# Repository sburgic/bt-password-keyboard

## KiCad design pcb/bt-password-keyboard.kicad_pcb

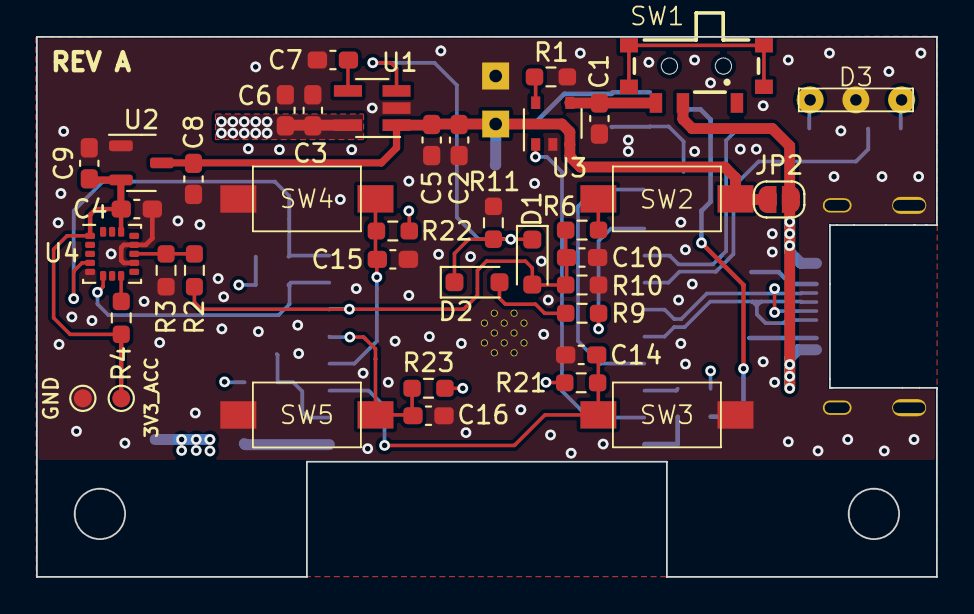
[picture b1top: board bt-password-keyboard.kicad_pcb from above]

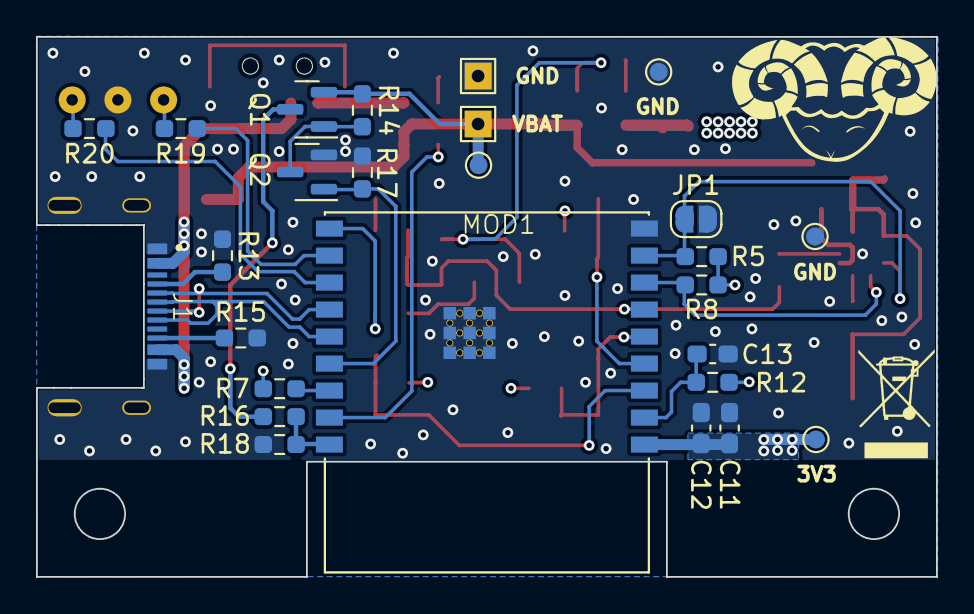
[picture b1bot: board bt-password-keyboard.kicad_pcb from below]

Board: 4 copper layers, 50.0 x 30.0 mm, 65 parts (26 on the bottom side), 35 nets.

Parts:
C1: 4,7uF; C_0603_1608Metric_Pad1.08x0.95mm_HandSolder
C2, C3, C11: 10uF; C_0603_1608Metric_Pad1.08x0.95mm_HandSolder
C4, C5, C6, C12, C14, C15, C16: 100nF; C_0603_1608Metric_Pad1.08x0.95mm_HandSolder
C7: 470pF; C_0603_1608Metric_Pad1.08x0.95mm_HandSolder
C8, C9, C10, C13: 1uF; C_0603_1608Metric_Pad1.08x0.95mm_HandSolder
D1, D2: 1N4148; D_SOD-323_HandSoldering
D3: GREEN/RED; TH GENERIC LED 3MM DUAL (RED 3D)
J1: USB4520-03-1-A; SMD USB4520-03-1-A
JP1, JP2: Jumper_2_Open; SolderJumper-2_P1.3mm_Open_RoundedPad1.0x1.5mm
MOD1: ESP32-C3-WROOM-02; SMD ESP32C3-WROOM-02
Q1: IRLML6402; SOT-23
Q2: IRLML0030; SOT-23
R1: 47K; R_0603_1608Metric_Pad0.98x0.95mm_HandSolder
R2, R6, R9: 1K; R_0603_1608Metric_Pad0.98x0.95mm_HandSolder
R3, R4, R14, R16, R17, R18: 100K; R_0603_1608Metric_Pad0.98x0.95mm_HandSolder
R5, R7, R8, R10, R21, R22, R23: 10K; R_0603_1608Metric_Pad0.98x0.95mm_HandSolder
R11: 1M; R_0603_1608Metric_Pad0.98x0.95mm_HandSolder
R12: 22K; R_0603_1608Metric_Pad0.98x0.95mm_HandSolder
R13, R15: 5K1; R_0603_1608Metric_Pad0.98x0.95mm_HandSolder
R19, R20: 3K3; R_0603_1608Metric_Pad0.98x0.95mm_HandSolder
SW1: WE-450404015514; SMD WE 450404015514
SW2, SW3, SW4, SW5: CLEAR; SMD GENERIC 2-PIN 3.6x6x2.5
TP1: VBAT; TestPoint_THTPad_1.5x1.5mm_Drill0.7mm
TP2: GND; TestPoint_THTPad_1.5x1.5mm_Drill0.7mm
TP3, TP4, TP5, TP6, TP7, TP8: TP-ROUND-SMD-2MM; TestPoint_Pad_D1.0mm
U1: TLV75733PDBVR; SOT-23-5_HandSoldering
U2: XC6206P331MR-G; SOT-23-3
U3: MCP73831T-2ACI/OT; TSOP-5_1.65x3.05mm_P0.95mm
U4: LIS3DHTR; LGA-16_3x3mm_P0.5mm_LayoutBorder3x5y

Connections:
+3V3: C3.1, C6.2, C11.1, C12.1, MOD1.1 (3V3), R5.1, R7.1, R8.1, R12.2, R21.2, R22.2, R23.2, TP3.1, U1.5 (OUT)
+3V3_ACC: C4.2, C9.1, R4.2, TP7.1, U2.2 (VO), U4.1 (VDD_IO), U4.14 (VDD)
ACC_INT: R2.2, R3.2, U4.11 (INT1)
GND: C1.2, C2.2, C3.2, C4.1, C5.1, C6.1, C7.2, C8.2, C9.2, C10.2, C11.2, C12.2, C13.1, C14.2, C15.2, C16.2, D3.2 (K), J1.A1_B12 (GND_A), J1.B1_A12 (GND_B), J1.S1 (SHELL_GND), J1.S2 (SHELL_GND), J1.S3 (SHELL_GND), J1.S4 (SHELL_GND), JP1.1 (A), MOD1.9 (GND), MOD1.19 (GND), Q2.2 (S), R1.1, R3.1, R10.2, R11.2, R13.1, R15.2, R17.1, R18.1, SW3.2, SW4.2, SW5.2, TP2.1, TP4.1, TP6.1, TP8.1, U1.2 (GND), U2.1 (GND), U3.2 (VSS), U4.5 (GND), U4.10 (RES), U4.12 (GND)
GPIO2: MOD1.16 (IO2), R7.2
GPIO8: MOD1.7 (IO8), R8.2, U4.6 (SDA/SDI/SDO)
GPIO9: JP1.2 (B), MOD1.8 (IO9), R5.2, U4.4 (SCL/SPC)
LATCH: MOD1.10 (IO10), R9.2
LED_GREEN: MOD1.11 (RXD), R19.1
LED_RED: MOD1.12 (TXD), R20.2
unnamed: D2.2 (A), R9.1
unnamed: D3.1 (A), R19.2
unnamed: D3.3 (A), R20.1
unnamed: J1.A5 (CC1), R13.2
unnamed: J1.B5 (CC2), R15.1
unnamed: C13.2, MOD1.2 (EN), R12.1
unnamed: Q1.3 (D), R16.2
unnamed: Q1.1 (G), Q2.3 (D), R14.1
unnamed: R6.1, SW2.1
unnamed: C7.1, U1.4 (NC)
unnamed: R1.2, U3.5 (PROG)
unnamed: C1.1, SW1.3, U3.4 (VDD)
unnamed: R4.1, U4.8 (CS)
PWR_EN: D1.1 (K), D2.1 (K), R11.1, U1.3 (EN)
STAT: MOD1.17 (IO1), U3.1 (STAT)
SW_1: C14.1, MOD1.3 (IO4), R21.1, SW3.1
SW_2: C15.1, MOD1.4 (IO5), R22.1, SW4.1
SW_3: C16.1, MOD1.5 (IO6), R23.1, SW5.1
SW_CTRL: C10.1, D1.2 (A), MOD1.6 (IO7), R2.1, R6.2, R10.1
USB_DN: J1.A7 (DN1), J1.B7 (DN2), MOD1.13 (IO18)
USB_DP: J1.A6 (DP1), J1.B6 (DP2), MOD1.14 (IO19)
VBAT: C2.1, C5.2, C8.1, JP2.2 (B), Q1.2 (S), R14.2, SW2.2, TP1.1, TP5.1, U1.1 (IN), U2.3 (VI), U3.3 (VBAT)
VMON: MOD1.18 (IO0), R16.1, R18.2
VMON_EN: MOD1.15 (IO3), Q2.1 (G), R17.2
VUSB: J1.A4_B9 (VBUS_A), J1.B4_A9 (VBUS_B), JP2.1 (A), SW1.2

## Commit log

2023-12-29 Add .gitignore
2023-12-29 Add PCB (rev. A)
2023-12-29 Add initial source code
2023-12-30 Add LED handler
2023-12-30 Rename bt-password-keyboard.c to main.c
2023-12-30 Blink LED on critical error
2023-12-30 Add configuration handler
2024-11-02 Move source files to components
2024-11-02 Add error handling at initialization of components
